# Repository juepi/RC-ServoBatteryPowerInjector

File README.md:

# RC-Model Battery Power Injector for HV Servos

**ATTENTION:** Before thinking of using this PCB, make sure your servo will be able to handle the full battery voltage of your RC model! This means in example 8.4V for 2S LiPo battery (or even more for HV LiPos).  
This small PCB allows you to directly power your servo from your RC-models battery. One PCB can handle up to 2 Servos, or you can break the PCB apart in the middle (make sure to cut through the bottom copper layer before breaking the PCB at the perforation) to save space if you only need a single HV-powered Servo.  

## Usage
First, add 2x3 2.54mm pinheaders to the PCB. In example, you could use Amphenol FCI part number 10129382-912003BLF (cut in half).
Solder the battery wires to the large round pads on the bottom of the PCB. They are marked with "+" and "-", so things should be fairly clear ;-)
Make sure to use an appropiate wire gauge, good high-torque servos for 1:10 models can take 4 amps or more at full stall, so you should at least use AWG 22 (0,25mm²) wires connected to you battery.

**ATTENTION:** Make sure to connect your servo and RX in the right position and direction (see PWM marking above) to avoid damaging your RX and/or servo.  

You have 2 more 2x1 connectors on the PCB which will allow you to connect - in example - a voltage sensing telemetry unit of your transmitter/receiver directly to the battery voltage.

have fun,  
Juergen

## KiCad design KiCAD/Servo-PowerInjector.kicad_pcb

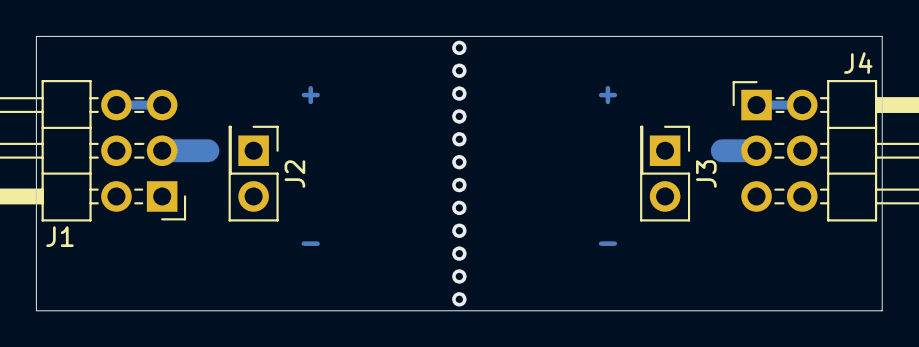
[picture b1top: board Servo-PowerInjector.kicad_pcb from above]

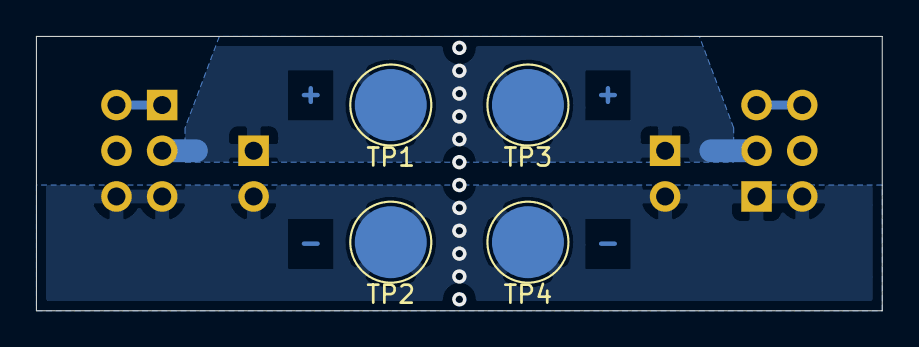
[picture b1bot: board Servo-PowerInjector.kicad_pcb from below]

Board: 2 copper layers, 47.0 x 15.2 mm, 8 parts (4 on the bottom side), 4 nets.

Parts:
J1, J4: Servo; PinHeader_2x03_P2.54mm_Horizontal
J2, J3: Pwr; PinHeader_2x01_P2.54mm_Vertical
TP1, TP2, TP3, TP4: Pwr; TestPoint_Pad_D4.0mm

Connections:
+BATT: J1.3, J2.1, J3.1, J4.3, TP1.1, TP3.1
GND: J1.1, J1.2, J2.2, J3.2, J4.5, J4.6, TP2.1, TP4.1
unnamed: J1.5, J1.6
unnamed: J4.1, J4.2
